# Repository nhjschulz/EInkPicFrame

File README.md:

# EInkPicFrame

The project builds an electronic picture frame using a 7 color E-Ink display.
It updates after an adjustable time period by reading images from an SD-Card.
The frame is powered from a battery and mimics a real picture frame by requiring
no power cable or a backlight. The software and hardware implements various power
saving methods to run for a long time without recharging.  

This is a hobbyist project. I have >20 years background in software development,
but lack the electronic engineering background. I'm using this project to
clear the fog in these mysterious regions below a HAL software layer. The project
therefore includes a hardware design as well.

## Requirements

A set of project requirements is collected here: [Requirements](design/Requirements.md)

## Concept

Block diagram of the system:

## Used Tools

The project is build using open source tools only. All of them are available for free. The following table shows the tools and versions used during development:

|Tool                  |   Usage                   | Version   | Link                                                               |
|----------------------|---------------------------|-----------|--------------------------------------------------------------------|
| Visual Studio Code   | Editor and IDE            | 1.63.2    | [https://code.visualstudio.com/](https://code.visualstudio.com/)   |
| PlatformIO           | Software build tools      | 5.2.4     | [https://platformio.org/](https://platformio.org/)                 |
| Python               | Script programming        | 3.10.1    | [https://www.python.org/](https://www.python.org/)                 |
| GIMP                 | Image Manipulation        | 2.10.30   | [https://www.gimp.org/](https://www.gimp.org/)                     |
| ImageMagick          | Image Manipulation        | 7.1.0     | [https://imagemagick.org/](https://imagemagick.org/)               |
| GIT                  | Version Control           | 2.19      | [https://git-scm.com/](https://git-scm.com/)                       |
| KiCad EDA            | Hardware Design           | 5.1.12    | [https://www.kicad.org//](https://www.kicad.org/)                  |

## Software Architecture

The implemented software architecture design is shown on the [Software Architecture](design/SwArchitecture.md) page.

## Hardware

The system is assembled using the following parts: [Partlist](design/Parts.md).

A description of the PCB developed for this project is described
here: [PCB](design/hardware.md).

## Image Generation

The images to show on the frame must be in a special raw format. The process to generate this format is
described on the [ImageConverter](imgconverter/howto.md) page.

## File System

The SD Card must be formated using a FAT file system. The software
expects a folder with the name "epd" on it. This folder contains
the following data:

      [epd]
       |---- [err]
       |---- [img]
       |---- epd.cfg

* The folder "err" holds error images that are displayed in case
  of a problem, like "low battery".
* The folder img holds your images in epd format.
* The file epd.cfg are the parameters for the display. See
  [Parameter File](./design/Parameter.md) for instructions to
  create it.

An example file system can be copied from the example
[File System](./design/FileSystem) folder.

## Prototype Progress

* 2021-12-11: System functional on breadboard (V1 hardware)

* 2021-01-22: V1 PCBs arrived and work

* 2022-02-01: First frame starts long run test in the living room

  Back side:

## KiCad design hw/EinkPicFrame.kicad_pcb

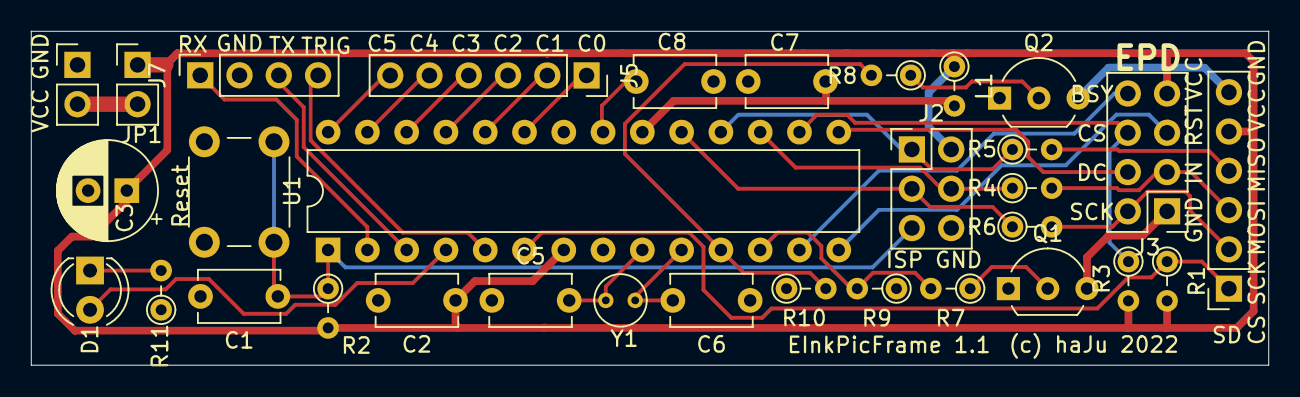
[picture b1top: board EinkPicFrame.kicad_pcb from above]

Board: 2 copper layers, 80.0 x 21.6 mm, 32 parts (0 on the bottom side), 36 nets.

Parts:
C1: 100 nF; C_Disc_D5.1mm_W3.2mm_P5.00mm
C2, C7, C8: 0.1 uF; C_Disc_D5.1mm_W3.2mm_P5.00mm
C3: CP; CP_Radial_D6.3mm_P2.50mm
C5, C6: 22 pF; C_Disc_D5.1mm_W3.2mm_P5.00mm
D1: LED; LED_D4.0mm
J1: SD; PinSocket_1x06_P2.54mm_Vertical
J2: AVR-ISP-6; PinHeader_2x03_P2.54mm_Vertical
J3: EPD; PinHeader_2x04_P2.54mm_Vertical
J4: Power; PinHeader_1x02_P2.54mm_Vertical
J5: PORTC; PinSocket_1x06_P2.54mm_Vertical
J7: Debug; PinSocket_1x04_P2.54mm_Vertical
JP1: Jumper; PinHeader_1x02_P2.54mm_Vertical
L1: 10 uH; R_Axial_DIN0204_L3.6mm_D1.6mm_P2.54mm_Vertical
Q1: 2N7000; TO-92L_Inline_Wide
Q2: 2N7000; TO-92_Inline_Wide
R1, R3, R9, R10: 1M; R_Axial_DIN0204_L3.6mm_D1.6mm_P2.54mm_Vertical
R2: 10K; R_Axial_DIN0204_L3.6mm_D1.6mm_P2.54mm_Vertical
R4, R5, R6, R11: 330; R_Axial_DIN0204_L3.6mm_D1.6mm_P2.54mm_Vertical
R7, R8: 180; R_Axial_DIN0204_L3.6mm_D1.6mm_P2.54mm_Vertical
SW1: SW_Push; SW_PUSH_6mm
U1: ATmega328P-PU; DIP-28_W7.62mm
Y1: Crystal; Crystal_C38-LF_D3.0mm_L8.0mm_Vertical

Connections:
+3V3: C2.1, C3.1, J1.5, J2.2, J3.7, JP1.1, L1.1, R1.2, R2.2, R3.2, U1.7
DPBUSY: J3.8, U1.13
DPCS: J3.6, R3.1, U1.16
DPDC: J3.4, U1.15
DPFET: R7.2, R9.2, U1.12
DPGND: J3.1, Q1.3
DPRST: J3.5, U1.14
GND: C1.2, C2.2, C3.2, C5.1, C6.1, C7.1, C8.2, J2.6, J4.1, J7.2, Q1.1, Q2.1, R9.1, R10.1, R11.1, SW1.1, U1.8, U1.22
LED: D1.2, U1.4
MISO: J1.4, R5.2
MOSI: J1.3, J3.3, R4.2
unnamed: C7.2, L1.2, U1.20
unnamed: C8.1, U1.21
unnamed: D1.1, R11.2
unnamed: J2.1, R5.1, U1.18
unnamed: J2.3, R6.1, U1.19
unnamed: J2.4, R4.1, U1.17
unnamed: J4.2, JP1.2
unnamed: J5.1, U1.23
unnamed: J5.2, U1.24
unnamed: J5.3, U1.25
unnamed: J5.4, U1.26
unnamed: J5.5, U1.27
unnamed: J5.6, U1.28
unnamed: Q1.2, R7.1
unnamed: Q2.2, R8.1
RESET: C1.1, J2.5, R2.1, SW1.2, U1.1
RXD: J7.1, U1.2
SCK: J1.2, J3.2, R6.2
SDCS: J1.1, R1.1, U1.6
SDFET: R8.2, R10.2, U1.11
SDGND: J1.6, Q2.3
TRIG: J7.4, U1.5
TXD: J7.3, U1.3
XTAL1: C5.2, U1.9, Y1.1
XTAL2: C6.2, U1.10, Y1.2

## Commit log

2021-12-02 Initial project skeleton
2021-12-02 Embedd plantuml SW Context diagram into readme
2021-12-03 Sketching a SW achitecture with PlantUML
2021-12-05 Fix typo in URL
2021-12-05 Update architecture.md
    Really fix typo
2021-12-06 Another try to fix Markdown Syntax
2021-12-09 Rough SW arcchitecture expressed in UML
2021-12-09 AVR SW environment setup
    * Atmel ICE programming in ISP mode working
    * "Blinky" app working on breadboard (LED on PB0)
2021-12-10 Updated design collateral
    Added first requirements
    Added initial parts list
2021-12-11 Added FatFS distribution to service layer
    Version R0.14.b from http://elm-chan.org/fsw/ff/00index_e.html
2021-12-13 Add a fixed size Queue buffer template.
    This is expected to be used together with serial debug output later.
2021-12-18 Queue: Provide buffer via constructor
    Changed Queue implementation to be initialized with a buffer instead of having an own one as second template parameter. This is more flexible in usage.
2021-12-18 UART: Added driver
    Added UART driver which will support debug logs in future.
2021-12-19 Debug: Added printf style debug over UART
2021-12-19 FatFS: Moved documentation from src to design
2021-12-20 Queue: Add forgotten include guard defines
2021-12-20 SPI: Add initial driver version
2021-12-21 Ticktimer: Inititial implementation
    User Timer0 to implement a 10ms tick timer.
2021-12-28 SpI: Added byte order ans pflash data support
2021-12-28 Debug: Fixed cpp vararg part
    Variable part now optional to allow printf style call with format only.
2021-12-28 Display: Added Driver code
    Init, Sleep and Clear are working.
2021-12-29 Doc: Started image conversion description
2021-12-29 Imgconv: Initial version
    Image get created but result not yet tested.
2021-12-30 ImgConverter: Included python script execution
2021-12-31 FatFS: Checkpoint 1st working version
    TODOs:
    * Interface with SPI diver (code manipulates register directly)
    * Coexistence with display SPI
2021-12-31 HW: Addind Pin assignment definition
2021-12-31 SPI: Support bot SDCard an Display
    Reconfigure SPI to a slave on each IO of this slave.
2022-01-01 HW: Started schematic with KiCad
2022-01-02 Doc: Added state maschine to architecture
2022-01-02 HW: Created PCB
2022-01-03 App: Added StateHandler class
2022-01-03 HW: Added possibility to add a crystal
2022-01-04 App: Added application skeleton
    * added app classes
    * Introducing StateManager
2022-01-04 Gpio: Introduced Gpio class
2022-01-04 Hal: Added CPU abstraction class
2022-01-05 Hal: Use Gpio class in services
    Stop modifying registers directly in services,
    Use Gpio abstraction from HAL.
2022-01-05 Tools: Fix format error check condition
    and -> or for width /height check
2022-01-05 HAL: Add CPU abstraction
2022-01-05 Service: Introduce Power cladd
2022-01-05 HAL: Remove stale header
2022-01-05 App: Use Halt() service on error
2022-01-05 HAL: Turn Gpio into static class
2022-01-05 Gen: Use new HAL service for CPU and GPIO
2022-01-05 Service: Fixed searcg/replace for Gpio access
    "set" functions got turned into "clr" by accident.
2022-01-06 HAL: Add Wakeup timer Timer2 driver to wakeup from power down mode
2022-01-06 HAL: Added cpu clock selection
2022-01-06 Doc: Added Power handling classes
2022-01-06 Service: Added APIs to control module powering
    SD Card and Display can be powered by Mosfets
2022-01-06 Service: Added Debug api for trigger pin
2022-01-08 HAL: UART Drain TX buffer before disabling
2022-01-08 HAL: Add power up/down to SPI
2022-01-08 HAL: Start with onchip peripherals powered off
2022-01-09 HAL: Add enable/disable power to TickTimer
2022-01-09 Service: Enable FatFS relative path and find option
2022-01-09 Service:; Add simple FileIo Wrapper for FatFS
2022-01-09 HAL: enable SPI 2X mode
    We only run a 1Mhz, so double speed should not be an issue.
2022-01-09 Service: Add resume from sleep
2022-01-09 Service: Mocved power related code to Power class
2022-01-09 App: Added Update State
    Added state that updates the picture once a day.
2022-01-11 FatFS: Removed redundant copy
2022-01-12 SPI: Tune Gpios for lowest power when off
2022-01-12 App: Move power resume to init state
    Service Init only sets default gpio state.
2022-01-12 App: Move display init to update state
    Was in power resume, but this does only enable onchip devices, not the display.
2022-01-14 App: Added power consumption test code
    Enable with -D WITH_POWER_TEST=1
2022-01-14 Cpu: Implement nonbusy delay function
    Function is called as Cpu::idle(x), where x is number of 10ms timer ticks
2022-01-14 Build: Added disassembly generation
2022-01-16 Hal: Set GPIO high/low before switching direction
    Avoids short glitches on chipselect lines
2022-01-16 Service: User power frindly sleep in display
2022-01-16 service: Added LED access
2022-01-16 service: Added idle() wait to Power class
2022-01-16 App: Blink Led as start indicator in initstate
2022-01-16 build: Ignore assembler listing file by git
2022-01-16 Cpu: Increase fast clock to 4 Mhz
    Increasig from 1 to 4 Mhz doesn't consume much more CPU current
    when busy. But it reduces SD-Card
    busy time from 12 to 4 seconds.
2022-01-18 Design: Added Low Battery detection
2022-01-19 HW: Ubgrade to KiCad 6.0
    Jut open project in Kicad 6 and save to new format.
2022-01-22 HAL: Add API to change SPI clock frequency
2022-01-22 HAL: Introduce HW revision
    Prepare switch from N-Mosfets to P-Mosfets for contolling power.
2022-01-22 Service: Set SPI clock to max for display IO
2022-01-22 Service: Fix SDCard init issue
    Repeate sending CMD0 for up to 10 times. Many cards don't respond on the first try.
    Don't wait for card ready
    in CMD0 case. Some cards
    don't signal it during init
    stage.
2022-01-22 HAL: Allow higher baud at 4Mhz CPU
    4Mhz works up to 19200
2022-01-22 ADC: Add capability to determine supply voltage
2022-01-23 Design: Update V1 prototype state
2022-01-29 HAL: Get down to >100 nA by driving IOs high
    IO's to SD and EPD need to be high during sleep.
    Otherwise current flows over the IOs as the FETs are
    low side switches.
    Current need dropped from 800 nA to < 100nA, which
    I cannot really measure anymore.
2022-01-30 HW: Revert to KiCad 5
    I have trouble getting 3d view to work wiht KiCad 6
2022-01-30 APP: Support Parameter file
    Add support for a parameter file to modify settings
    like the picture update interval and voltage settings.
2022-01-30 Tools: Support palette reording in epdconv.py
    The palette color in imags can be in any order. Add a dynamic
    mapping to the order required by the display. This reording is
    for example needed when converting images with ImageMagick.
2022-01-31 Design: Reworked Statemachine for LowBattery
    Fixed state transitions around LowBattery state
2022-02-01 App: Add LowPower state
    Check supply voltage in init and when leaving sleep.
    Enter lowPower mode if voltage is below the minimum
    voltage parameter level.
    The LowPower state displays a charge image and
    keeps sleeping until voltage raised above the
    minimum again.
2022-02-02 IMGCNV: Tuned clear color to better match EPD
    The '8th' color of the EPD is the "clear" one. It is
    used to clean the display but is a color darker than
    white, close to white human skin. So it is good to
    have in the palette. This change adjust it to better
    match the display. The value before was a little to
    blue.
2022-02-02 FILESYS: Added skeleton
    EPD expects a a epd folder with specific subfolders on
    the SD card. Added a folder with an example how it has to be setup.
2022-02-02 Doc: Updated readme showing 1st build picture frame
2022-02-02 DOC: Typos fixed
2022-02-06 HW: ADC + Small improvements (V1.1)
    Added proper wiring for AVCC and AREF according to data sheet
    * 100 nF capacitor to ground on AREF
    * 10 uH inductor on AVCC
    Added header for unused PortC pins
    * May be used as 2nd SPI (bit bang)
    * Independent SPI would allow to power EPD and SD independently
2022-02-06 CHECK: Enabled cppcheck
    and fixed the findings
2022-02-06 Added push CI build github action
2022-02-06 Actions: Fix typo in pio run
2022-02-06 Rename DIsplay.h to Display.h
    Linux build support
2022-02-07 HW: Add PCB description
2022-02-08 Doc: Describe ImageMagick img manipulation
    This is an commandline alternative to using GIMP.
2022-02-13 App: Improve error handling
    * Detect missing EPD by having timeouts on init (no hang forever)
    * Blink LED 10 times on EPD error
    * Display red screen if EPD responsive during an error
    * Power down system after error display on screen or led
2022-02-13 Doc: Update documentation to reflect current state
2022-02-24 FileIo: Use void * for read buffer parameter
    changed fro uint8_t* to allow read into any type address.
2022-02-24 Param: Read over FileIo API not FatFS directly
2022-02-24 HAL: Drive wakeup timer from external crystal
    Change Timer2 (Wakeup timer) to run asynchronously from a 32.768 kHz
    crystal. This allows the CPU to really enter power safe mode.
    Aleep current dropped from 100 uA (5v) to something I cannot measure
    anymore.
2022-02-24 Unittest: Fix compilation issue
2022-03-03 ErrorState: Enable display power for red screen
    Display must be powered to switch to red error screen.
2022-03-06 Power: Rework sleep power handling
    Keep SD and Display power in sync
    * Both use the same SPI signal lines
    * Disabling only one cause current draw of IO lines when low
    Improve time management
    * add millis counter to TickTimer
    * compensate sleep durations in tick counter when timer is stopped
2022-03-15 Design: Document pins uses for watch crystal
    The crystal is needed for power safe mode.
    Internal clock otherwise keeps running in power safe mode.
2022-03-15 TickTimer: Improve accuracy
    10ms is is 156.25 interrupts at 4 Mhz CPU.
    Count 1 cycle more every 4 cycles.
2022-03-19 Power: Low Battery state fixes
    Debugging low battery detection using an
    adjustable power supply showed to issues
    * Integer overflow computing milliseconds for 10min duration
    Math was done using 16bit, needed to add ul suffix to force 32bit
    * Reassignment to a reference variable is not working. Use pointer
    instead
2022-04-02 Sleep: Fix sleep loops calculation
    Ensure milliseconds are computed in 32 bits to avoid overflows.
2022-04-03 Add SD-CARD change detection
    Compare volume serial number at wakeup with the one read at startup.
    Reset system if card was swapped.
2022-04-05 Update README.md
    typo fixes
2022-11-09 Update SwArchitecture.md
    typos ...
2022-11-09 Update SwArchitecture.md
    typo :(
2022-11-09 Update SwArchitecture.md
    typo
2024-06-19 DOC: Fix arrows in class diagram
    Wrong notation was used for "use" relation.
    Need dashed lines.
2025-11-08 chore; spelling nd trailing newline
2025-11-08 build: fix github CI pipelline
    bump actions/cache from V2 tp V4 as V2 is EOL.
2025-11-08 build: use v4 actions for checkout and cache
    Former V2 deprecated
2025-11-08 build: typo in pipeline yaml
2025-11-08 update pipeline script on master (#1)
    * build: fix github CI pipelline
    bump actions/cache from V2 tp V4 as V2 is EOL.
2025-11-08 build: move to action/cache@4
2025-12-23 PIO: Fix Atmel ICE upload command
    Update upload command for Atmel ICE as the old syntax didn't work anymore.
2025-12-23 fix: Update epdcfg.py for crc
    The interface of the CRC library has changed (v7.1.0).
    Adjust edcfg.py accordingly.
